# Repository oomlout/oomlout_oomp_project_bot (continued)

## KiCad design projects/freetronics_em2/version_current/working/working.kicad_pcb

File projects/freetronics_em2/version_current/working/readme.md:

# EM2 by freetronics  
This is a harvested standardized copy of a project from github.  
The original project can be found at:  
https://github.com/freetronics/EM2  
Please consult that link for additional, details, files, and license information.  
Note: It was auto harvested and if the original repo had more than one board file or anything out of the ordinary the files here are likely not representative.

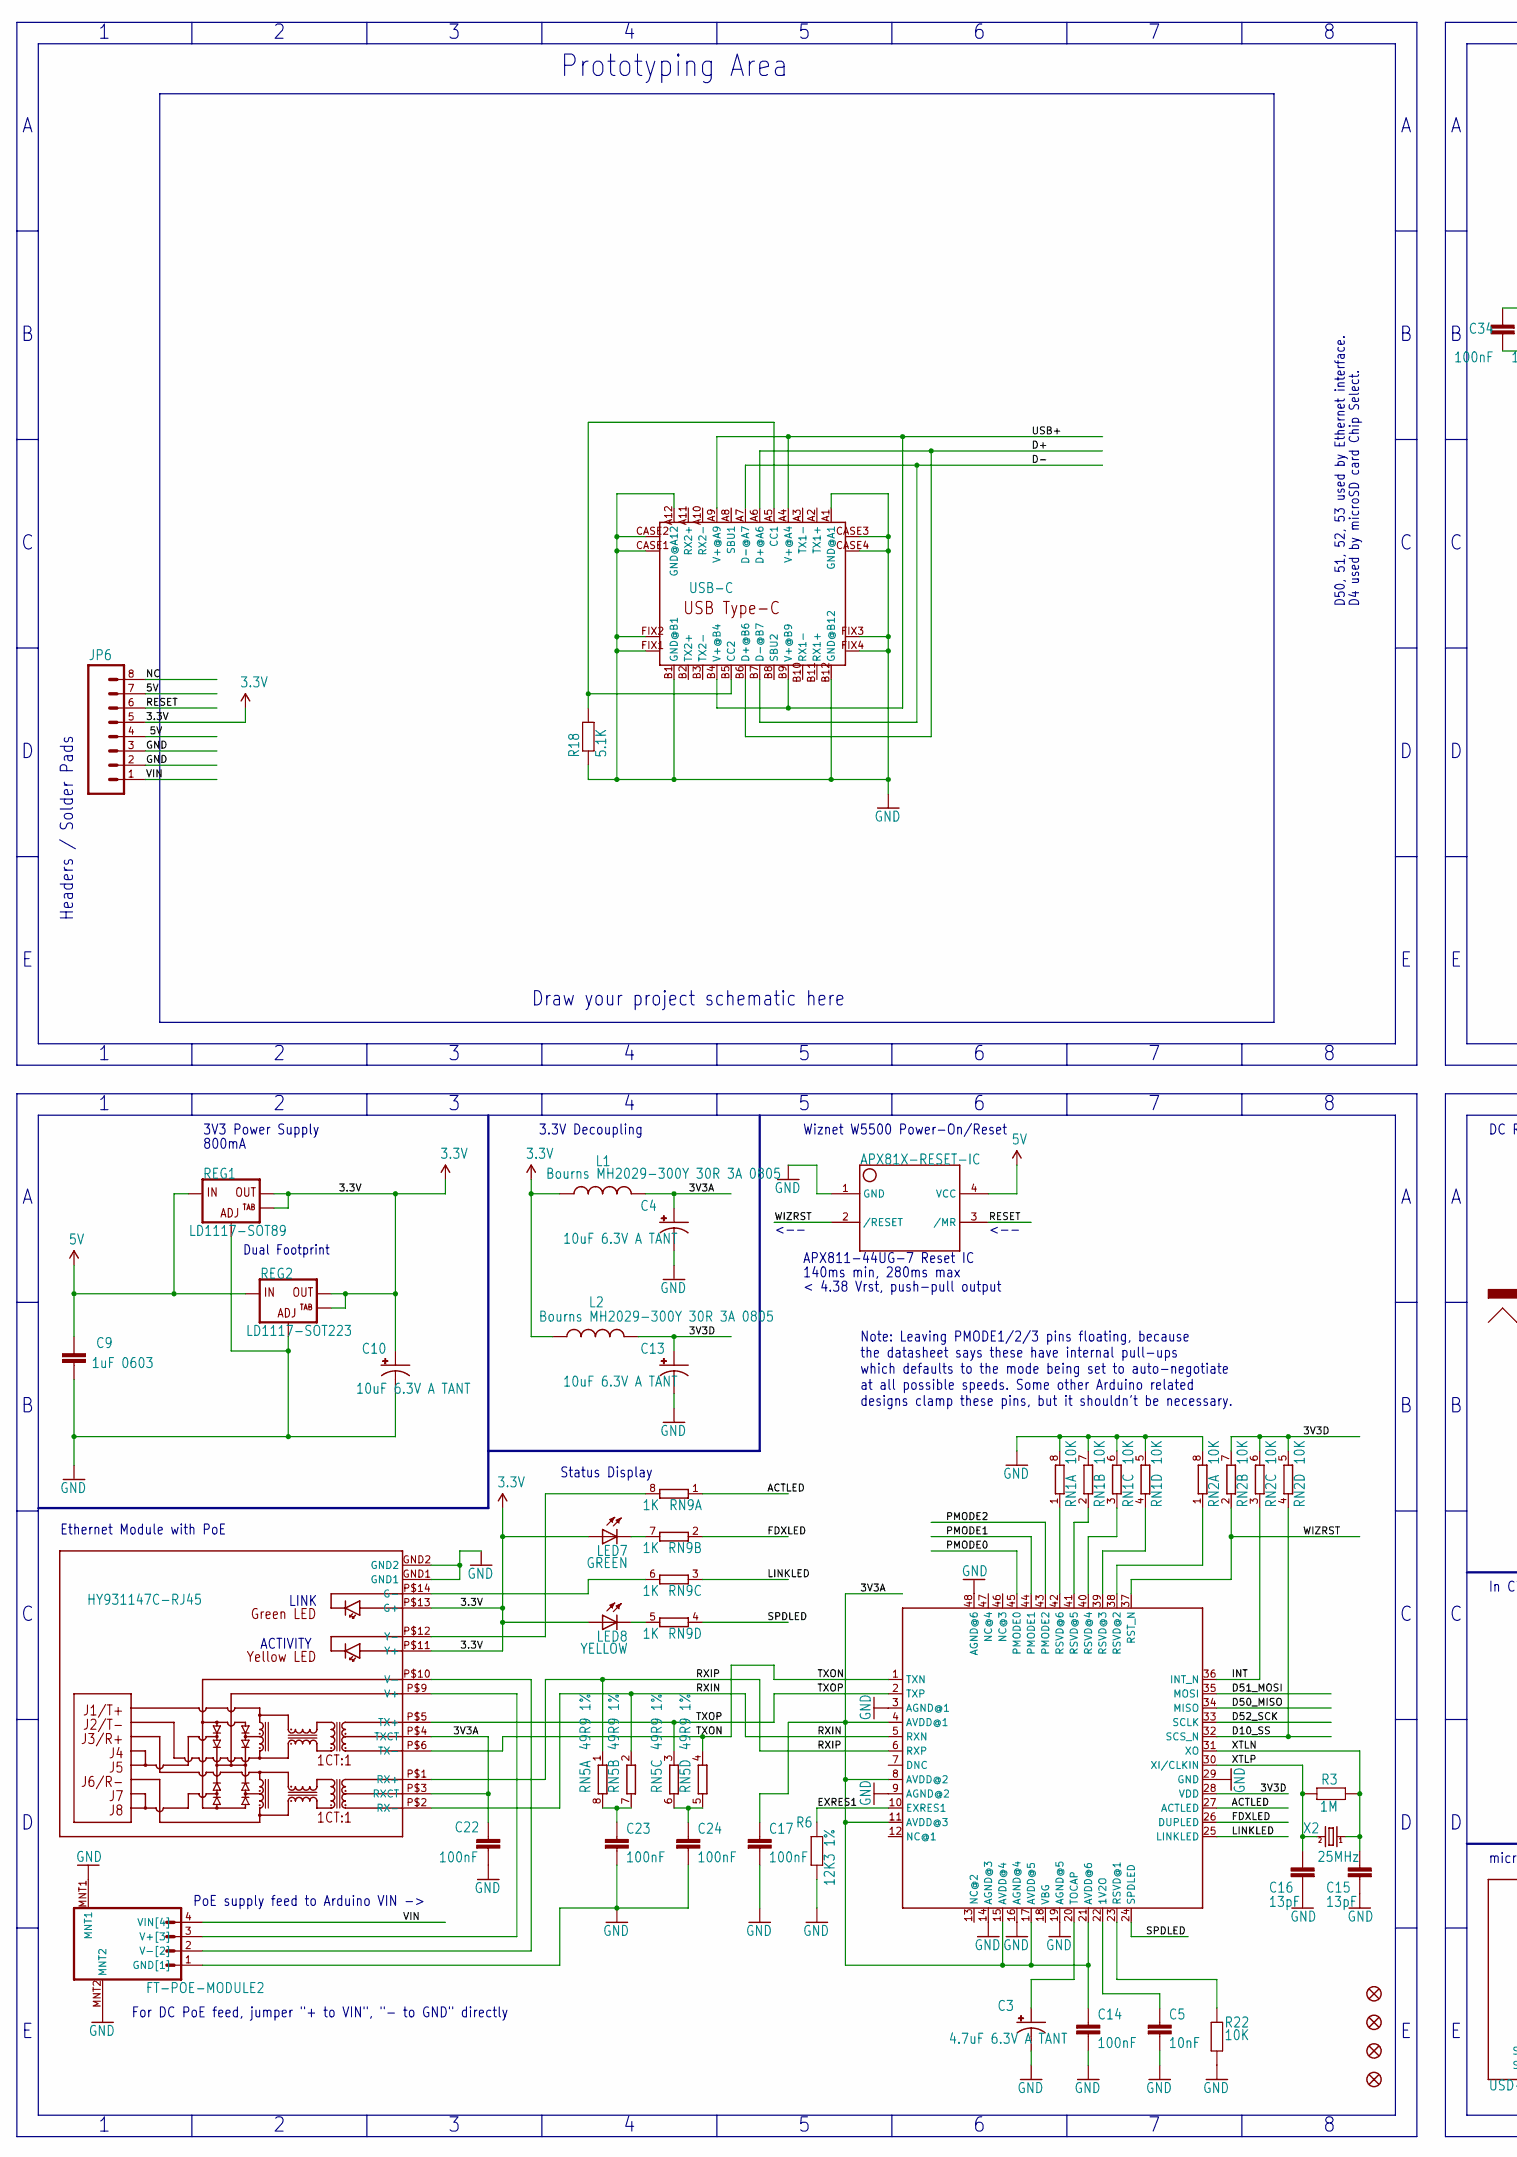
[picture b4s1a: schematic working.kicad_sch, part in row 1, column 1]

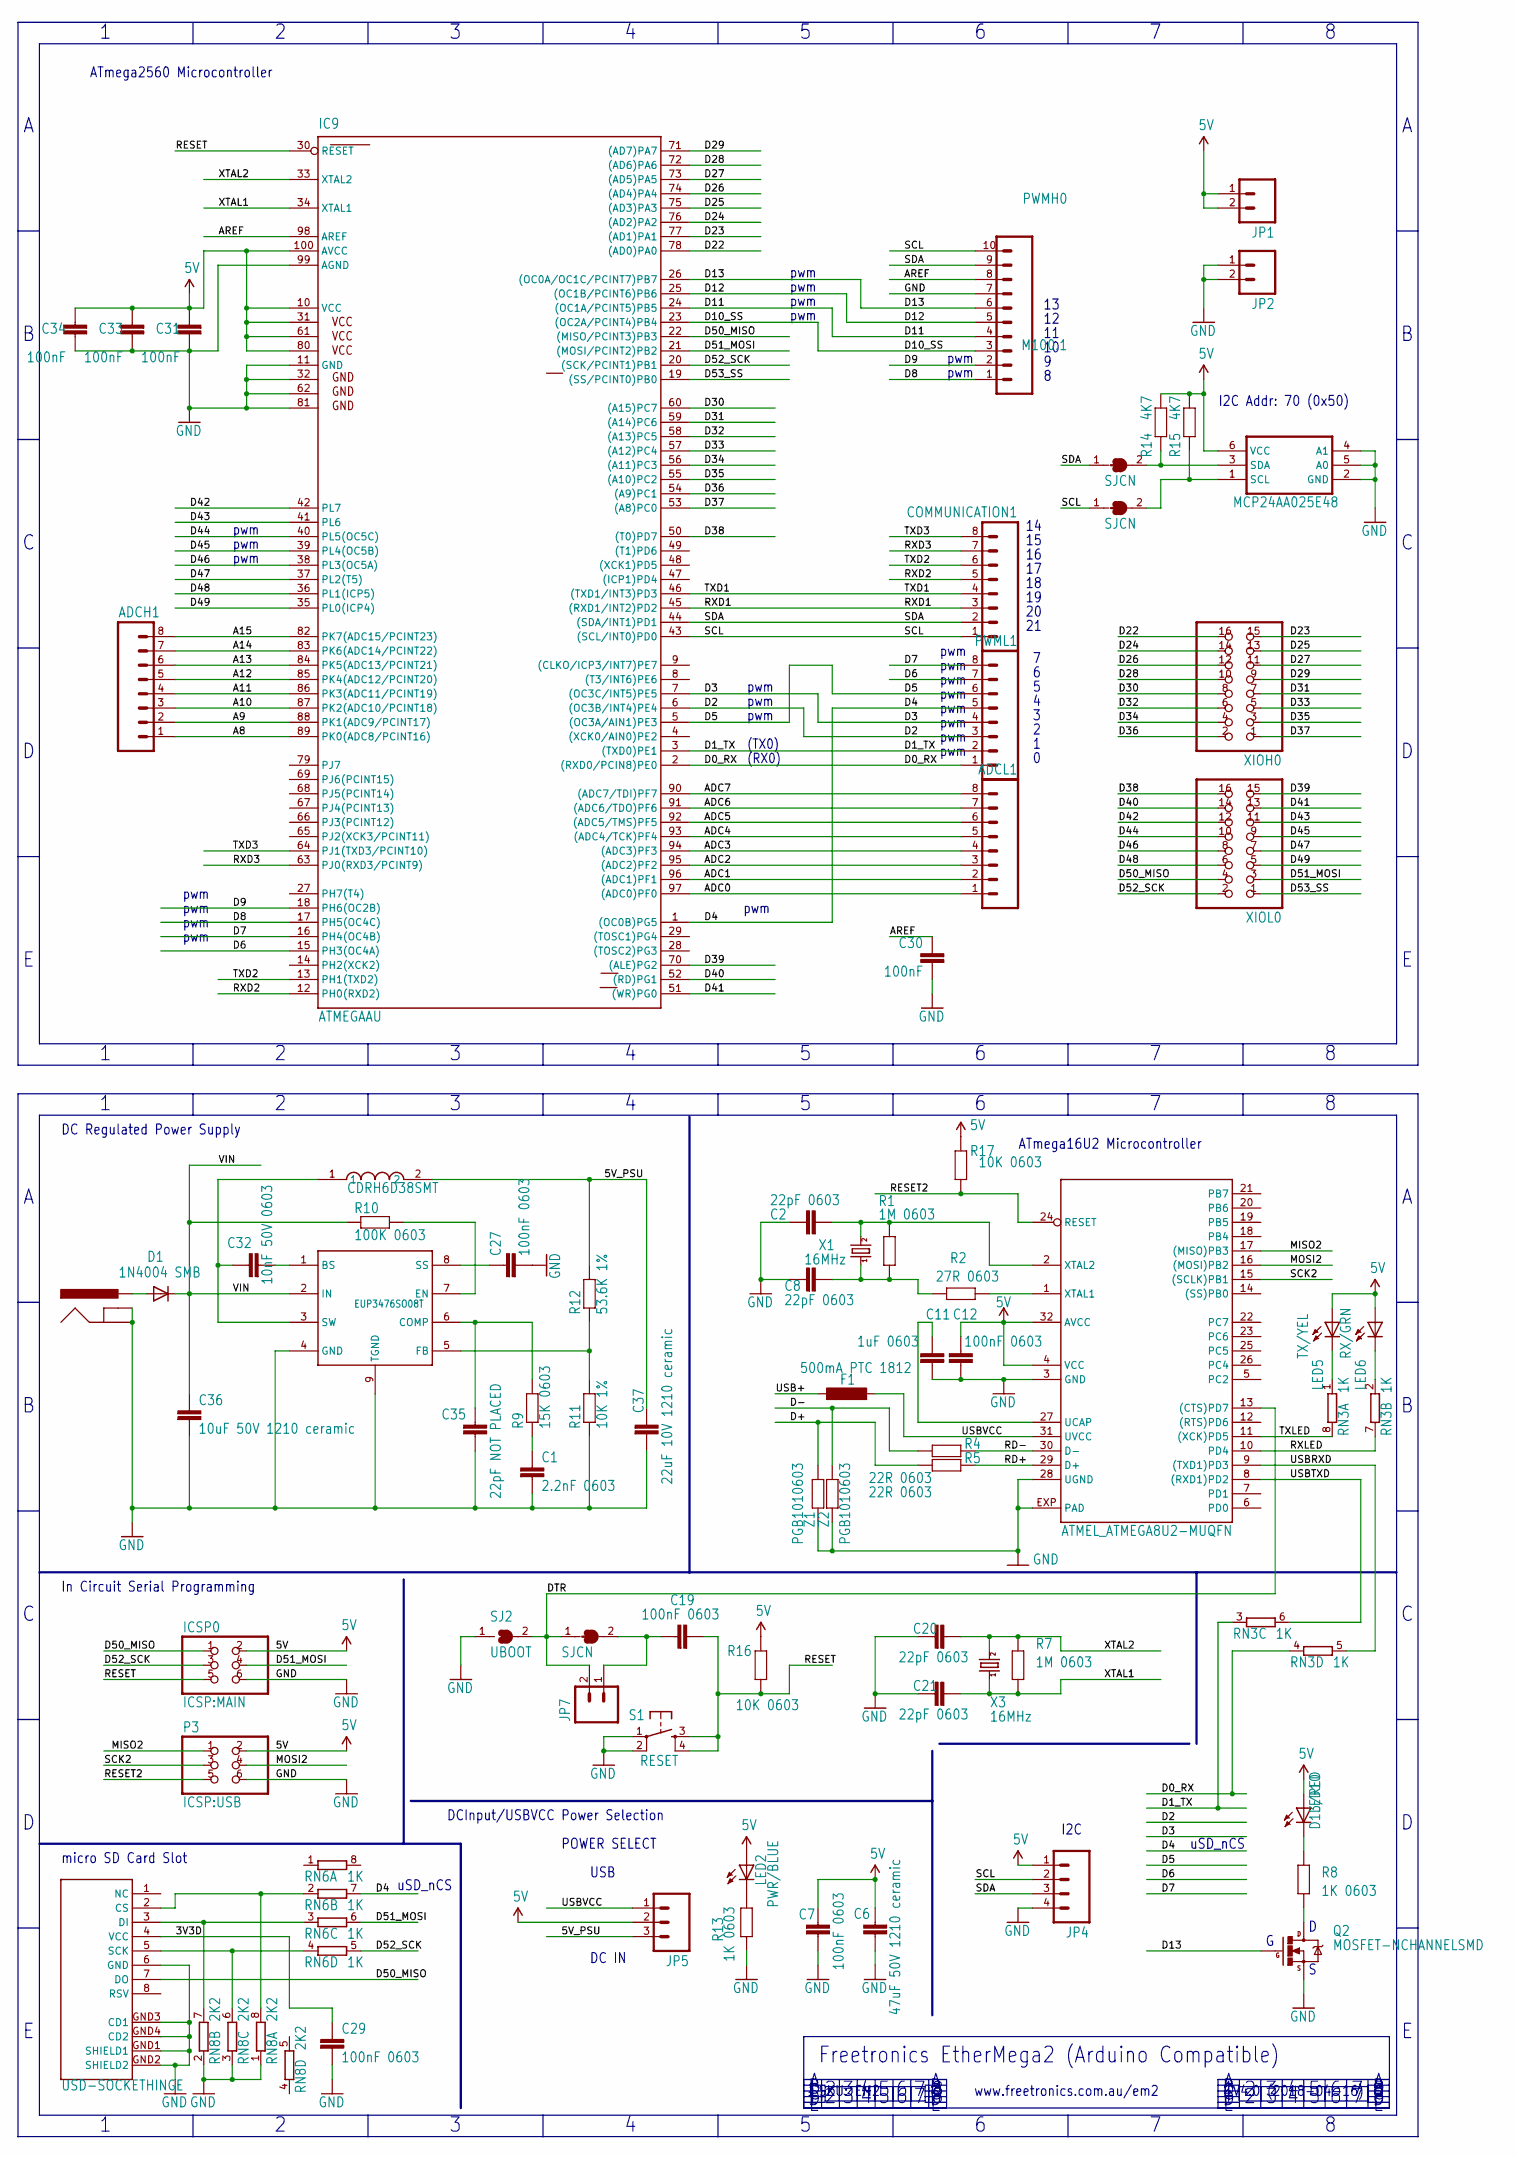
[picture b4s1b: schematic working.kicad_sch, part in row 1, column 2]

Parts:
ADCH1: M08STD; 1X08
ADCL1: M08STD; 1X08
C1: 2.2nF 0603; 0603
C2, C8, C20, C21: 22pF 0603; 0603
C3: 4.7uF 6.3V A TANT; EIA3216
C4, C10, C13: 10uF 6.3V A TANT; EIA3216
C5: 10nF; 0603
C6: 47uF 50V 1210 ceramic; C1210
C7, C12, C19, C27, C29: 100nF 0603; 0603
C9, C11: 1uF 0603; 0603
C14, C17, C22, C23, C24, C30, C31, C33, C34: 100nF; 0603
C15, C16: 13pF; 0603
C32: 10nF 50V 0603; 0603
C35: 22pF NOT PLACED; 0603
C36: 10uF 50V 1210 ceramic; C1210
C37: 22uF 10V 1210 ceramic; C1210
COMMUNICATION1: M08STD; 1X08
D1: 1N4004 SMB; SMB-DIODE
F1: 500mA PTC 1812; L1812
FID1, FID2, FID3, FID4: FIDUCIAL1X2.5; FIDUCIAL-1X2.5
IC1: EUP3476SO08T; SO08T
IC2: APX81X-RESET-IC; SOT143-R
IC3: ATMEL_ATMEGA8U2-MUQFN; ATMEL_QFN32
IC4: MCP24AA025E48; SOT23-6
IC6: W5500
IC9: ATMEGAAU; TQFP100
ICSP0: ICSP:MAIN; 2X03
J1: POWER_JACKPTH_SLOTS; POWER_JACK_PTH_SLOTS
JP1, JP2, JP7: M02PTH; 1X02
JP3: FT-POE-MODULE2; FT-POE-MODULE-CLEAN
JP4: M04PTH; 1X04
JP5: M03PTH; 1X03
JP6: M08STD; 1X08
L1, L2: Bourns MH2029-300Y 30R 3A 0805; L2012C
L4: CDRH6D38SMT; CDRH
LED2: PWR/BLUE; LED-0603
LED5: TX/YEL; LED-0603
LED6: RX/GRN; LED-0603
LED7: GREEN; LED-0603
LED8: YELLOW; LED-0603
LED10: D13/RED; LED-0603
P3: ICSP:USB; 2X03
P4: USD-SOCKETHINGE; MOLEX-SD-500901-003
PWMH0: M100.1; 1X10
PWML1: M08STD; 1X08
Q2: MOSFET-NCHANNELSMD; SOT23-3
R1, R7: 1M 0603; 0603
R2: 27R 0603; 0603
R3: 1M; 0603
R4, R5: 22R 0603; 0603
R6: 12K3 1%; 0603
R8, R13: 1K 0603; 0603
R9: 15K 0603; 0603
R10: 100K 0603; 0603
R11: 10K 1%; 0603
R12: 53.6K 1%; 0603
R14, R15: 4K7; 0603
R16, R17: 10K 0603; 0603
R18: 5.1K; 0603
R22: 10K; 0603
REG1: LD1117-SOT89; SOT89
REG2: LD1117-SOT223; SOT223
RN1, RN2: 10K; CAY16
RN3, RN6, RN9: 1K; CAY16
RN5: 49R9 1%; CAY16
RN8: 2K2; CAY16
S1: RESET; TACTILE_SWITCH_SMD
SJ2: UBOOT; SJ
SJ3, SJ5, SJ6: SJCN; SJC
U1: HY931147C-RJ45; HY931147C
U$15: USB-C; USB-C-U52A
X1, X3: 16MHz; HC49U-V
X2: 25MHz; HC49U-V
XIOH0: PINHD-2X8; 2X08
XIOL0: PINHD-2X8; 2X08
Z1, Z2: PGB1010603; 0603

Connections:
3.3V: C10.A (+), JP6.5, L1.1, L2.1, LED7.A, LED8.A, REG1.2 (OUT), REG1.4 (OUT@1), REG2.2 (OUT), REG2.4 (OUT@1), U1.P$11 (Y+), U1.P$13 (G+)
3V3A: C4.A (+), C14.1, C17.1, C22.1, IC6.4 (AVDD@1), IC6.8 (AVDD@2), IC6.11 (AVDD@3), IC6.15 (AVDD@4), IC6.17 (AVDD@5), IC6.21 (AVDD@6), L1.2, U1.P$3 (RXCT), U1.P$4 (TXCT)
3V3D: C13.A (+), C29.1, IC6.28 (VDD), L2.2, P4.4 (VCC), RN2.5 (2), RN2.6 (2), RN2.7 (2)
5V: C6.2, C7.1, C9.1, C12.1, C31.1, C33.1, C34.1, IC2.4 (VCC), IC3.4 (VCC), IC3.32 (AVCC), IC4.6 (VCC), IC9.10 (VCC), IC9.31 (VCC1), IC9.61 (VCC2), IC9.80 (VCC3), IC9.100 (AVCC), ICSP0.2, JP1.1, JP1.2, JP4.1, JP5.2, JP6.4, JP6.7, LED2.A, LED5.A, LED6.A, LED10.A, P3.2, R14.1, R15.1, R16.2, R17.2, REG1.3 (IN), REG2.3 (IN)
5V_PSU: C37.1, JP5.3, L4.2, R12.2
A8: ADCH1.1, IC9.89 (PK0(ADC8/PCINT16))
A9: ADCH1.2, IC9.88 (PK1(ADC9/PCINT17))
A10: ADCH1.3, IC9.87 (PK2(ADC10/PCINT18))
A11: ADCH1.4, IC9.86 (PK3(ADC11/PCINT19))
A12: ADCH1.5, IC9.85 (PK4(ADC12/PCINT20))
A13: ADCH1.6, IC9.84 (PK5(ADC13/PCINT21))
A14: ADCH1.7, IC9.83 (PK6(ADC14/PCINT22))
A15: ADCH1.8, IC9.82 (PK7(ADC15/PCINT23))
ACTLED: IC6.27 (ACTLED), RN9.1
ADC0: ADCL1.1, IC9.97 ((ADC0)PF0)
ADC1: ADCL1.2, IC9.96 ((ADC1)PF1)
ADC2: ADCL1.3, IC9.95 ((ADC2)PF2)
ADC3: ADCL1.4, IC9.94 ((ADC3)PF3)
ADC4: ADCL1.5, IC9.93 ((ADC4/TCK)PF4)
ADC5: ADCL1.6, IC9.92 ((ADC5/TMS)PF5)
ADC6: ADCL1.7, IC9.91 ((ADC6/TDO)PF6)
ADC7: ADCL1.8, IC9.90 ((ADC7/TDI)PF7)
AREF: C30.1, IC9.98 (AREF), PWMH0.8
D0_RX: IC9.2 ((RXD0/PCIN8)PE0), PWML1.1, RN3.4 (1)
D1_TX: IC9.3 ((TXD0)PE1), PWML1.2, RN3.3 (1)
D2: IC9.6 ((OC3B/INT4)PE4), PWML1.3
D3: IC9.7 ((OC3C/INT5)PE5), PWML1.4
D4: IC9.1 ((OC0B)PG5), PWML1.5, RN6.7 (2)
D5: IC9.5 ((OC3A/AIN1)PE3), PWML1.6
D6: IC9.15 (PH3(OC4A)), PWML1.7
D7: IC9.16 (PH4(OC4B)), PWML1.8
D8: IC9.17 (PH5(OC4C)), PWMH0.1
D9: IC9.18 (PH6(OC2B)), PWMH0.2
D10_SS: IC6.32 (SCS_N), IC9.23 ((OC2A/PCINT4)PB4), PWMH0.3, RN2.4 (1)
D11: IC9.24 ((OC1A/PCINT5)PB5), PWMH0.4
D12: IC9.25 ((OC1B/PCINT6)PB6), PWMH0.5
D13: IC9.26 ((OC0A/OC1C/PCINT7)PB7), PWMH0.6, Q2.1 (G)
D22: IC9.78 ((AD0)PA0), XIOH0.16
D23: IC9.77 ((AD1)PA1), XIOH0.15
D24: IC9.76 ((AD2)PA2), XIOH0.14
D25: IC9.75 ((AD3)PA3), XIOH0.13
D26: IC9.74 ((AD4)PA4), XIOH0.12
D27: IC9.73 ((AD5)PA5), XIOH0.11
D28: IC9.72 ((AD6)PA6), XIOH0.10
D29: IC9.71 ((AD7)PA7), XIOH0.9
D30: IC9.60 ((A15)PC7), XIOH0.8
D31: IC9.59 ((A14)PC6), XIOH0.7
D32: IC9.58 ((A13)PC5), XIOH0.6
D33: IC9.57 ((A12)PC4), XIOH0.5
D34: IC9.56 ((A11)PC3), XIOH0.4
D35: IC9.55 ((A10)PC2), XIOH0.3
D36: IC9.54 ((A9)PC1), XIOH0.2
D37: IC9.53 ((A8)PC0), XIOH0.1
D38: IC9.50 ((T0)PD7), XIOL0.16
D39: IC9.70 ((ALE)PG2), XIOL0.15
D40: IC9.52 ((RD)PG1), XIOL0.14
D41: IC9.51 ((WR)PG0), XIOL0.13
D42: IC9.42 (PL7), XIOL0.12
D43: IC9.41 (PL6), XIOL0.11
D44: IC9.40 (PL5(OC5C)), XIOL0.10
D45: IC9.39 (PL4(OC5B)), XIOL0.9
D46: IC9.38 (PL3(OC5A)), XIOL0.8
D47: IC9.37 (PL2(T5)), XIOL0.7
D48: IC9.36 (PL1(ICP5)), XIOL0.6
D49: IC9.35 (PL0(ICP4)), XIOL0.5
D50_MISO: IC6.34 (MISO), IC9.22 ((MISO/PCINT3)PB3), ICSP0.1, P4.7 (DO), XIOL0.4
D51_MOSI: IC6.35 (MOSI), IC9.21 ((MOSI/PCINT2)PB2), ICSP0.4, RN6.6 (2), XIOL0.3
D52_SCK: IC6.33 (SCLK), IC9.20 ((SCK/PCINT1)PB1), ICSP0.3, RN6.5 (2), XIOL0.2
D53_SS: IC9.19 ((SS/PCINT0)PB0), XIOL0.1
D+: R5.2, U$15.A6 (D+@A6), U$15.B6 (D+@B6), Z1.1
D-: R4.2, U$15.A7 (D-@A7), U$15.B7 (D-@B7), Z2.1
DTR: IC3.13 ((CTS)PD7), JP7.2, SJ2.2, SJ3.1
EXRES1: IC6.10 (EXRES1), R6.2
FDXLED: IC6.26 (DUPLED), RN9.2 (1)
GND: C1.2, C2.1, C3.C (-), C4.C (-), C5.2, C6.1, C7.2, C8.1, C9.2, C10.C (-), C11.2, C12.2, C13.C (-), C14.2, C15.2, C16.2, C17.2, C20.1, C21.1, C22.2, C23.2, C24.2, C27.2, C29.2, C30.2, C31.2, C33.2, C34.2, C35.2, C36.2, C37.2, IC1.4 (GND), IC1.9 (TGND), IC2.1 (GND), IC3.3 (GND), IC3.28 (UGND), IC3.EXP (PAD), IC4.2 (GND), IC4.4 (A1), IC4.5 (A0), IC6.3 (AGND@1), IC6.9 (AGND@2), IC6.14 (AGND@3), IC6.16 (AGND@4), IC6.19 (AGND@5), IC6.29 (GND), IC6.48 (AGND@6), IC9.11 (GND), IC9.32 (GND1), IC9.62 (GND2), IC9.81 (GND3), IC9.99 (AGND), ICSP0.6, J1.GND, J1.GNDBREAK, JP2.1, JP2.2, JP3.1 (GND[1]), JP3.MNT1, JP3.MNT2, JP4.4, JP6.2, JP6.3, P3.6, P4.6 (GND), P4.GND1 (SHIELD1), P4.GND2 (SHIELD2), P4.GND3 (CD1), P4.GND4 (CD2), PWMH0.7, Q2.2 (S), R6.1, R11.1, R13.1, R18.1, R22.1, REG1.1 (ADJ), REG2.1 (ADJ), RN1.5 (2), RN1.6 (2), RN1.7 (2), RN1.8 (2), RN2.8 (2), RN8.1, RN8.2 (1), RN8.3 (1), S1.1, S1.2, SJ2.1, U1.GND1, U1.GND2, U$15.A1 (GND@A1), U$15.A12 (GND@A12), U$15.B1 (GND@B1), U$15.B12 (GND@B12), U$15.CASE1 (GND@CASE1), U$15.CASE2 (GND@CASE2), U$15.CASE3 (GND@CASE3), U$15.CASE4 (GND@CASE4), U$15.FIX1 (GND@FIX1), U$15.FIX2 (GND@FIX2), U$15.FIX3 (GND@FIX3), U$15.FIX4 (GND@FIX4), Z1.2, Z2.2
INT: IC6.36 (INT_N), RN2.3 (1)
LINKLED: IC6.25 (LINKLED), RN9.3 (1)
MISO2: IC3.17 ((MISO)PB3), P3.1
MOSI2: IC3.16 ((MOSI)PB2), P3.4
unnamed: C24.1, RN5.5 (2), RN5.6 (2)
unnamed: LED10.C, R8.2
unnamed: Q2.3 (D), R8.1
unnamed: IC3.1 (XTAL1), R2.1
unnamed: IC4.1 (SCL), R15.2, SJ6.2
unnamed: LED6.C, RN3.2 (1)
unnamed: LED2.C, R13.2
unnamed: LED5.C, RN3.1
unnamed: IC4.3 (SDA), R14.2, SJ5.2
unnamed: P4.5 (SCK), RN6.4 (1), RN8.6 (2)
unnamed: P4.2 (CS), RN6.2 (1), RN8.8 (2)
unnamed: P4.3 (DI), RN6.3 (1), RN8.7 (2)
unnamed: LED8.C, RN9.5 (2)
unnamed: RN9.6 (2), U1.P$14 (G-)
unnamed: D1.A, J1.PWR
unnamed: IC6.39 (RSVD@3), RN1.4 (1)
unnamed: IC6.40 (RSVD@4), RN1.3 (1)
unnamed: C27.1, IC1.8 (SS)
unnamed: C1.1, R9.1
unnamed: C35.1, IC1.6 (COMP), R9.2
unnamed: R18.2, U$15.A5 (CC1), U$15.B5 (CC2)
unnamed: JP3.3 (V+[3]), U1.P$9 (V+)
unnamed: JP3.2 (V-[2]), U1.P$10 (V-)
unnamed: C32.1, IC1.3 (SW), L4.1
unnamed: C32.2, IC1.1 (BS)
unnamed: IC1.7 (EN), R10.2
unnamed: IC6.41 (RSVD@5), RN1.2 (1)
unnamed: C19.1, JP7.1, SJ3.2
unnamed: IC6.42 (RSVD@6), RN1.1
unnamed: IC1.5 (FB), R11.2, R12.1
unnamed: IC6.23 (RSVD@1), R22.2
unnamed: IC6.38 (RSVD@2), RN2.1
unnamed: C5.1, IC6.22 (1V2O)
unnamed: C3.A (+), IC6.20 (TOCAP)
unnamed: C2.2, IC3.2 (XTAL2), R1.2, X1.2
unnamed: C8.2, R1.1, R2.2, X1.1
unnamed: C11.1, IC3.27 (UCAP)
unnamed: C23.1, RN5.7 (2), RN5.8 (2)
unnamed: LED7.C, RN9.7 (2)
unnamed: RN9.8 (2), U1.P$12 (Y-)
NC: JP6.8
PMODE0: IC6.45 (PMODE0)
PMODE1: IC6.44 (PMODE1)
PMODE2: IC6.43 (PMODE2)
RD+: IC3.29 (D+), R5.1
RD-: IC3.30 (D-), R4.1
RESET: C19.2, IC2.3 (/MR), IC9.30 (RESET), ICSP0.5, JP6.6, R16.1, S1.3, S1.4
RESET2: IC3.24 (RESET), P3.5, R17.1
RXD1: COMMUNICATION1.3, IC9.45 ((RXD1/INT2)PD2)
RXD2: COMMUNICATION1.5, IC9.12 (PH0(RXD2))
RXD3: COMMUNICATION1.7, IC9.63 (PJ0(RXD3/PCINT9))
RXIN: IC6.5 (RXN), RN5.2 (1), U1.P$2 (RX-)
RXIP: IC6.6 (RXP), RN5.1, U1.P$1 (RX+)
RXLED: IC3.10 (PD4), RN3.7 (2)
SCK2: IC3.15 ((SCLK)PB1), P3.3
SCL: COMMUNICATION1.1, IC9.43 ((SCL/INT0)PD0), JP4.2, PWMH0.10, SJ6.1
SDA: COMMUNICATION1.2, IC9.44 ((SDA/INT1)PD1), JP4.3, PWMH0.9, SJ5.1
SPDLED: IC6.24 (SPDLED), RN9.4 (1)
TXD1: COMMUNICATION1.4, IC9.46 ((TXD1/INT3)PD3)
TXD2: COMMUNICATION1.6, IC9.13 (PH1(TXD2))
TXD3: COMMUNICATION1.8, IC9.64 (PJ1(TXD3/PCINT10))
TXLED: IC3.11 ((XCK)PD5), RN3.8 (2)
TXON: IC6.1 (TXN), RN5.4 (1), U1.P$6 (TX-)
TXOP: IC6.2 (TXP), RN5.3 (1), U1.P$5 (TX+)
USB+: F1.1, U$15.A4 (V+@A4), U$15.A9 (V+@A9), U$15.B4 (V+@B4), U$15.B9 (V+@B9)
USBRXD: IC3.9 ((TXD1)PD3), RN3.5 (2)
USBTXD: IC3.8 ((RXD1)PD2), RN3.6 (2)
USBVCC: F1.2, IC3.31 (UVCC), JP5.1
VIN: C36.1, D1.C, IC1.2 (IN), JP3.4 (VIN[4]), JP6.1, R10.1
WIZRST: IC2.2 (/RESET), IC6.37 (RST_N), RN2.2 (1)
XTAL1: C21.2, IC9.34 (XTAL1), R7.1, X3.1
XTAL2: C20.2, IC9.33 (XTAL2), R7.2, X3.2
XTLN: C15.1, IC6.31 (XO), R3.1, X2.1
XTLP: C16.1, IC6.30 (XI/CLKIN), R3.2, X2.2

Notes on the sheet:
pwm
Freetronics EtherMega2 (Arduino Compatible)
140ms min, 280ms max
POWER SELECT
Dual Footprint
<--
uSD_nCS
www.freetronics.com.au/em2
D4 used by microSD card Chip Select.
ACTIVITY
< 4.38 Vrst, push-pull output
ATmega2560 Microcontroller
Wiznet W5500 Power-On/Reset
Status Display
Draw your project schematic here
(RX0)
LINK
Note: Leaving PMODE1/2/3 pins floating, because the datasheet says these have internal pull-ups which defaults to the mode being set to auto-negotiate at all possible speeds. Some other Arduino related designs clamp these pins, but it shouldn't be necessary.
Prototyping Area
Headers / Solder Pads
In Circuit Serial Programming
I2C
USB
PoE supply feed to Arduino VIN ->
DC Regulated Power Supply
V4.0 (2018-04-16)
DC IN
I2C Addr: 70 (0x50)
SKU: EM2
800mA
ATmega16U2 Microcontroller
Ethernet Module with PoE
micro SD Card Slot
For DC PoE feed, jumper "+ to VIN", "- to GND" directly
(TX0)
3.3V Decoupling
DCInput/USBVCC Power Selection
3V3 Power Supply
APX811-44UG-7 Reset IC
D50, 51, 52, 53 used by Ethernet interface.

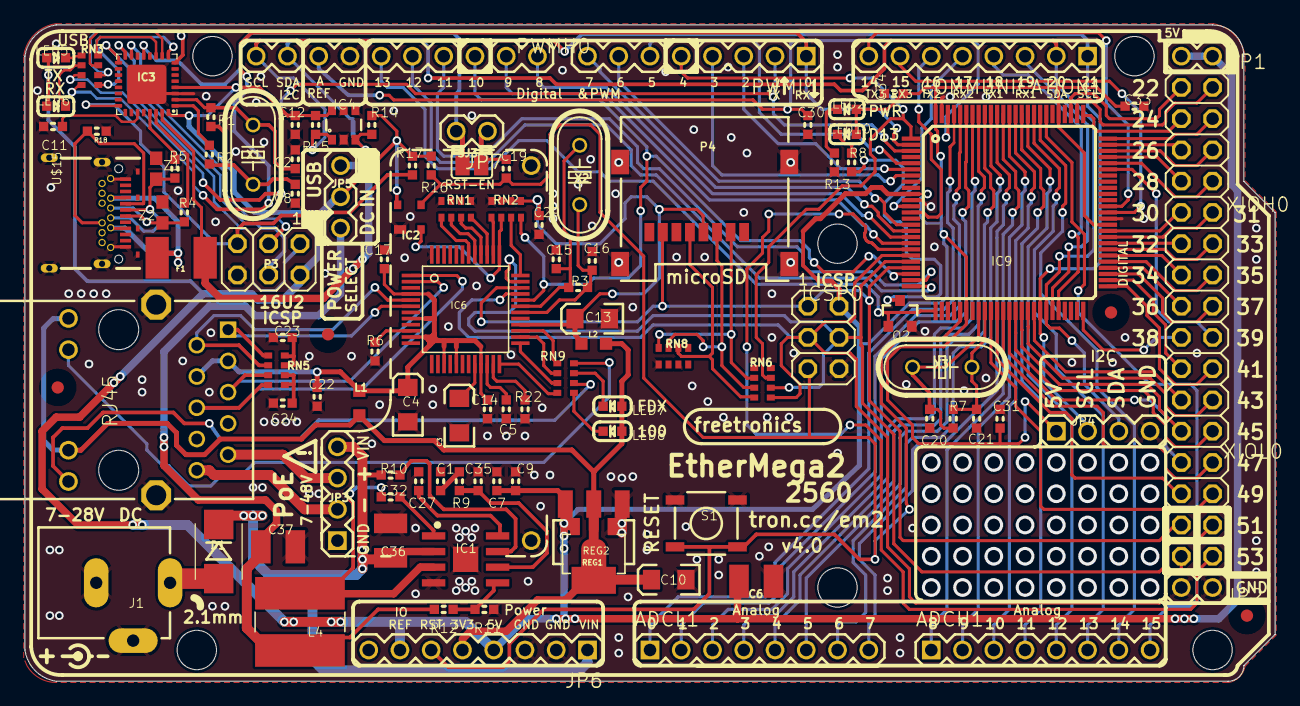
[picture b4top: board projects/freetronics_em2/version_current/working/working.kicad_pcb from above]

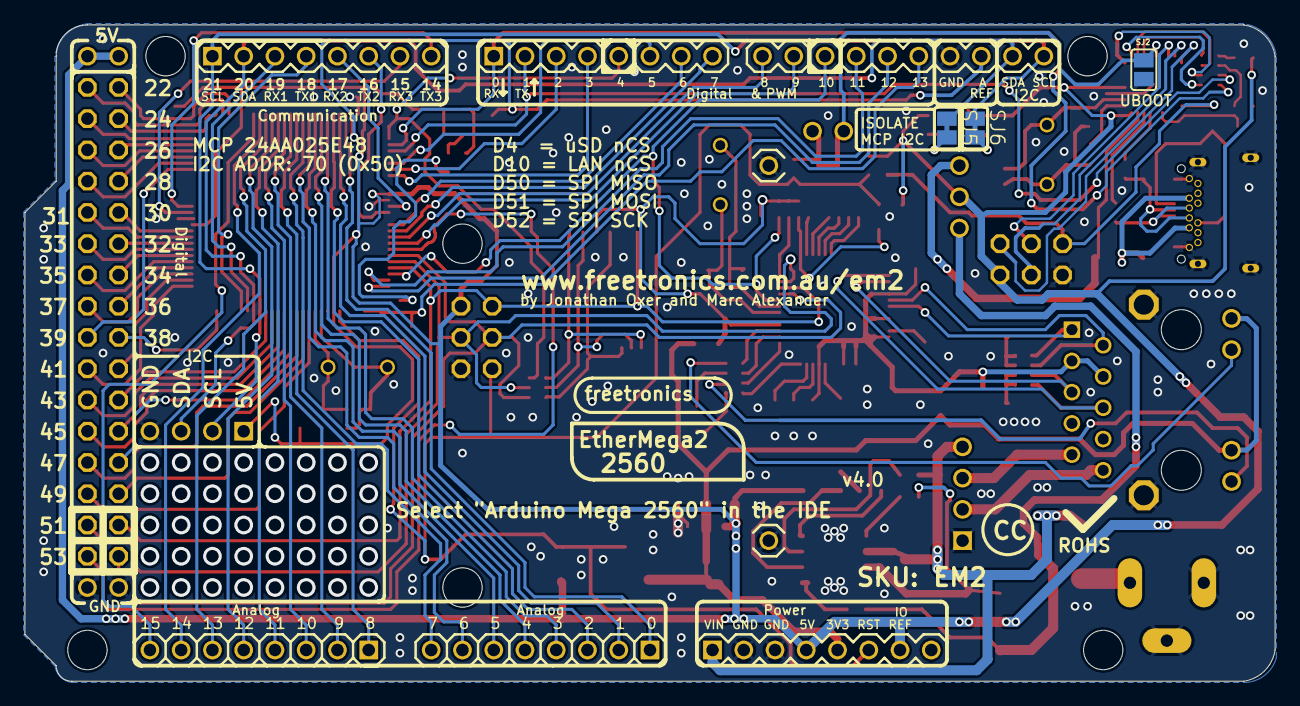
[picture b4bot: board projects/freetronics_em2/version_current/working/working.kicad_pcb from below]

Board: 2 copper layers, 101.6 x 53.3 mm, 119 parts (3 on the bottom side), 149 nets.

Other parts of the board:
@HOLE0, @HOLE1, @HOLE2, @HOLE3, @HOLE4, @HOLE5: (no value)

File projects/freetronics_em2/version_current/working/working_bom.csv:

"Id";"Designator";"Footprint";"Quantity";"Designation";"Supplier and ref";
1;"@HOLE4,@HOLE5,@HOLE3,@HOLE0,@HOLE2,@HOLE1";"";6;"";;;
2;"C15,C16";"0603";2;"13pF";;;
3;"X1,X3";"HC49U-V";2;"16MHz";;;
4;"P3";"2X03";1;"ICSP:USB";;;
5;"RN8";"CAY16";1;"2K2";;;
6;"C29,C12,C7,C27,C19";"0603";5;"100nF 0603";;;
7;"R4,R5";"0603";2;"22R 0603";;;
8;"IC4";"SOT23-6";1;"MCP24AA025E48";;;
9;"C35";"0603";1;"22pF NOT PLACED";;;
10;"LED7";"LED-0603";1;"GREEN";;;
11;"PWMH0";"1X10";1;"";;;
12;"RN3,RN6,RN9";"CAY16";3;"1K";;;
13;"JP4";"1X04";1;"";;;
14;"XIOH0,XIOL0";"2X08";2;"";;;
15;"C5";"0603";1;"10nF";;;
16;"REG1";"SOT89";1;"LD1117-SOT89";;;
17;"IC1";"SO08T";1;"EUP3476SO08T";;;
18;"R11";"0603";1;"10K 1%";;;
19;"ADCH1,ADCL1,JP6,COMMUNICATION1,PWML1";"1X08";5;"";;;
20;"C23,C14,C30,C24,C31,C22,C34,C33,C17";"0603";9;"100nF";;;
21;"C8,C20,C2,C21";"0603";4;"22pF 0603";;;
22;"R12";"0603";1;"53.6K 1%";;;
23;"LED6";"LED-0603";1;"RX/GRN";;;
24;"JP1,JP7,JP2";"1X02";3;"";;;
25;"S1";"TACTILE_SWITCH_SMD";1;"RESET";;;
26;"RN5";"CAY16";1;"49R9 1%";;;
27;"R13,R8";"0603";2;"1K 0603";;;
28;"Z2,Z1";"0603";2;"PGB1010603";;;
29;"C36";"C1210";1;"10uF 50V 1210 ceramic";;;
30;"LED2";"LED-0603";1;"PWR/BLUE";;;
31;"R22";"0603";1;"10K";;;
32;"IC3";"ATMEL_QFN32";1;"ATMEGA16U2-MU";;;
33;"IC6";"W5500";1;"W5500";;;
34;"U1";"HY931147C";1;"HY931147C-RJ45";;;
35;"R14,R15";"0603";2;"4K7";;;
36;"FID1,FID3,FID4,FID2";"FIDUCIAL-1X2.5";4;"FIDUCIAL1X2.5";;;
37;"R1,R7";"0603";2;"1M 0603";;;
38;"F1";"L1812";1;"500mA PTC 1812";;;
39;"L1,L2";"L2012C";2;"Bourns MH2029-300Y 30R 3A 0805";;;
40;"R9";"0603";1;"15K 0603";;;
41;"R17,R16";"0603";2;"10K 0603";;;
42;"L4";"CDRH";1;"CDRH6D38SMT";;;
43;"U$15";"USB-C-U52A";1;"USB-C";;;
44;"R2";"0603";1;"27R 0603";;;
45;"C11,C9";"0603";2;"1uF 0603";;;
46;"LED8";"LED-0603";1;"YELLOW";;;
47;"D1";"SMB-DIODE";1;"1N4004 SMB";;;
48;"C32";"0603";1;"10nF 50V 0603";;;
49;"REG2";"SOT223";1;"LD1117-SOT223";;;
50;"IC9";"TQFP100";1;"ATMEGA2560-16AU";;;
51;"C37";"C1210";1;"22uF 10V 1210 ceramic";;;
52;"LED5";"LED-0603";1;"TX/YEL";;;
53;"C13,C4,C10";"EIA3216";3;"10uF 6.3V A TANT";;;
54;"JP3";"FT-POE-MODULE-CLEAN";1;"FT-POE-MODULE";;;
55;"X2";"HC49U-V";1;"25MHz";;;
56;"P4";"MOLEX-SD-500901-003";1;"microSD";;;
57;"RN1,RN2";"CAY16";2;"10K";;;
58;"R6";"0603";1;"12K3 1%";;;
59;"SJ3";"SJC";1;"RESET-EN";;;
60;"R10";"0603";1;"100K 0603";;;
61;"J1";"POWER_JACK_PTH_SLOTS";1;"DC_2_1MM";;;
62;"ICSP0";"2X03";1;"ICSP:MAIN";;;
63;"R3";"0603";1;"1M";;;
64;"JP5";"1X03";1;"";;;
65;"C1";"0603";1;"2.2nF 0603";;;
66;"Q2";"SOT23-3";1;"2N7002";;;
67;"C6";"C1210";1;"47uF 50V 1210 ceramic";;;
68;"R18";"0603";1;"5.1K";;;
69;"LED10";"LED-0603";1;"D13/RED";;;
70;"C3";"EIA3216";1;"4.7uF 6.3V A TANT";;;
71;"IC2";"SOT143-R";1;"APX811-44UG-7";;;
72;"SJ2";"SJ";1;"UBOOT";;;
73;"SJ6,SJ5";"SJC";2;"";;;

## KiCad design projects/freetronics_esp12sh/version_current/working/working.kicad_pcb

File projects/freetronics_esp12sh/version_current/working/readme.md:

# ESP12SH by freetronics  
This is a harvested standardized copy of a project from github.  
The original project can be found at:  
https://github.com/freetronics/ESP12SH  
Please consult that link for additional, details, files, and license information.  
Note: It was auto harvested and if the original repo had more than one board file or anything out of the ordinary the files here are likely not representative.

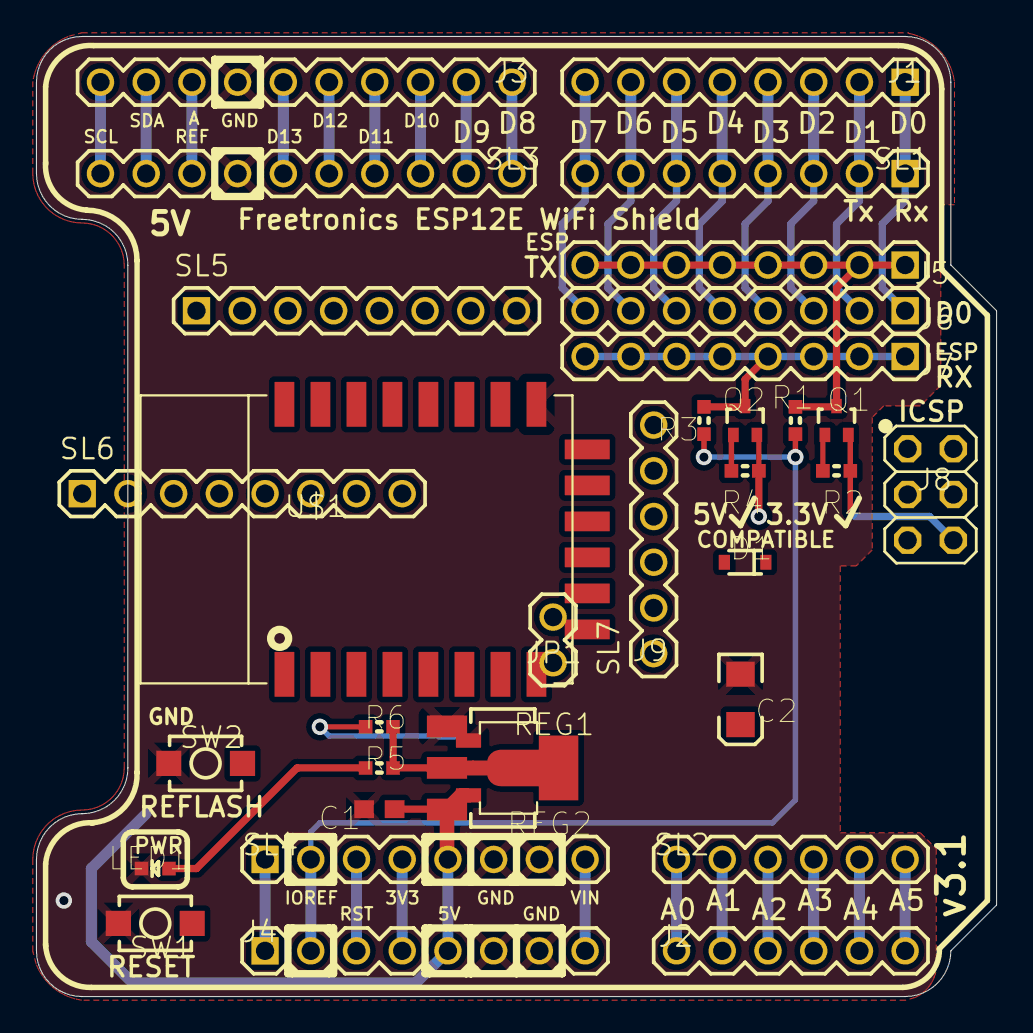
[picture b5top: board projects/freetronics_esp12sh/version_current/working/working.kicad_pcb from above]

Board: 2 copper layers, 53.3 x 53.3 mm, 34 parts (1 on the bottom side), 56 nets.

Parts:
C1: 1uF 0603; 0603
C2: 10uF 6.3V A TANT; EIA3216
D1: 1N4148WS; SOD-323
J1, J6: Digital_0_7; 1X08
J2: Analog; 1X06
J3: Digital_8_13; 1X10
J4: Power; 1X08
J5: BT-TX; 1X08
J7: BT-RX; 1X08
J8: ICSP; 2X03PTH
JP1: RST-LNK; 1X02
LED1: BLUE; LED-0603
Q1, Q2: RJU003N03 N-MOSFET; SOT32-3
R1, R2, R3, R4, R6: 10K; 0603
R5: 2K2; 0603
REG1: LD1117-SOT89; SOT89
REG2: LD1117-SOT223; SOT223
SJ1: ENABLE; SJC
SL1: Digital_0_7; 1X08
SL2, SL7: Analog; 1X06
SL3: Digital_8_13; 1X10
SL4: Power; 1X08
SL5, SL6: 5V; 1X08
SW1: RESET; TACTILE_SWITCH_SMD_2PIN_TINY
SW2: REFLASH; TACTILE_SWITCH_SMD_2PIN_TINY
U$1: ESP12ESMT; ESP12E

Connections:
3.3V: C2.A, Q1.1, Q2.1, R2.2, R4.2, R5.2, R6.2, REG1.2, REG1.4, REG2.2, REG2.4, SL6.8, U$1.8
5V: C1.1, J4.5, REG1.3, REG2.3, SL4.5
A0: J2.1, SL2.1
A1: J2.2, SL2.2
A2: J2.3, SL2.3
A3: J2.4, SL2.4
A4: J2.5, SL2.5
A5: J2.6, SL2.6
AREF: J3.8, SL3.8
CH_PD: SJ1.2, SL6.3, U$1.3
D0_RX: J1.1, J6.1, SL1.1
D1_TX: J1.2, J6.2, SL1.2
D2: J1.3, J6.3, SL1.3
D3: J1.4, J6.4, SL1.4
D4: J1.5, J6.5, SL1.5
D5: J1.6, J6.6, SL1.6
D6: J1.7, J6.7, SL1.7
D7: J1.8, J6.8, SL1.8
D8: J3.1, SL3.1
D9: J3.2, SL3.2
D10: J3.3, SL3.3
D11_MOSI: J3.4, SL3.4
D12_MISO: J3.5, SL3.5
D13_SCK: J3.6, SL3.6
GND: C1.2, C2.C, J3.7, J4.6, J4.7, J8.6, LED1.C, REG1.1, REG2.1, SL3.7, SL4.6, SL4.7, SL5.8, SW1.2, SW2.2, U$1.15
GPIO0: SL5.5, SW2.1, U$1.18
GPIO2: SL5.6, U$1.17
IOREF: J4.2, R1.2, R3.2, SL4.2
unnamed: SL7.1, U$1.9
unnamed: SL7.2, U$1.10
unnamed: SL7.3, U$1.11
unnamed: SL7.4, U$1.12
unnamed: LED1.A, R5.1
unnamed: SL7.5, U$1.13
unnamed: SL7.6, U$1.14
unnamed: SL5.7, U$1.16
unnamed: SL5.4, U$1.19
unnamed: SL5.3, U$1.20
unnamed: SL6.2, U$1.2
unnamed: SL6.4, U$1.4
unnamed: SL6.5, U$1.5
unnamed: SL6.6, U$1.6
unnamed: SL6.7, U$1.7
unnamed: J4.4, SL4.4
unnamed: R6.1, SJ1.1
unnamed: D1.1, JP1.2
NC: J4.1, SL4.1
RESET: J4.3, J8.5, JP1.1, SL4.3, SW1.1
RST: D1.2, SL6.1, U$1.1
RX: J7.1, J7.2, J7.3, J7.4, J7.5, J7.6, J7.7, J7.8, Q2.3, R3.1
RXD: Q2.2, R4.1, SL5.2, U$1.21
SCL: J3.10, SL3.10
SDA: J3.9, SL3.9
TX: J5.1, J5.2, J5.3, J5.4, J5.5, J5.6, J5.7, J5.8, Q1.3, R1.1
TXD: Q1.2, R2.1, SL5.1, U$1.22
VIN: J4.8, SL4.8

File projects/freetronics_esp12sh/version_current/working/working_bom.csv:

"Id";"Designator";"Footprint";"Quantity";"Designation";"Supplier and ref";
1;"R3,R6,R1,R4,R2";"0603";5;"10K";;;
2;"SL6,SL5";"1X08";2;"5V";;;
3;"J2,SL2,SL7";"1X06";3;"Analog";;;
4;"R5";"0603";1;"2K2";;;
5;"J4,SL4";"1X08";2;"Power";;;
6;"C2";"EIA3216";1;"10uF 6.3V A TANT";;;
7;"SW2";"TACTILE_SWITCH_SMD_2PIN_TINY";1;"REFLASH";;;
8;"Q1,Q2";"SOT32-3";2;"RJU003N03 N-MOSFET";;;
9;"JP1";"1X02";1;"RST-LNK";;;
10;"J3,SL3";"1X10";2;"Digital_8_13";;;
11;"J1,SL1,J6";"1X08";3;"Digital_0_7";;;
12;"U$1";"ESP12E";1;"ESP12ESMT";;;
13;"REG1";"SOT89";1;"LD1117-SOT89";;;
14;"J5";"1X08";1;"BT-TX";;;
15;"D1";"SOD-323";1;"1N4148WS";;;
16;"C1";"0603";1;"1uF 0603";;;
17;"J8";"2X03PTH";1;"ICSP";;;
18;"SW1";"TACTILE_SWITCH_SMD_2PIN_TINY";1;"RESET";;;
19;"J7";"1X08";1;"BT-RX";;;
20;"LED1";"LED-0603";1;"BLUE";;;
21;"REG2";"SOT223";1;"LD1117-SOT223";;;
22;"SJ1";"SJC";1;"ENABLE";;;
